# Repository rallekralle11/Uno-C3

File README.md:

Not intented as a wireless dev board but since it doesn't cost extra i added a crappy monopole antenna anyway. plenty of leftover space for it.

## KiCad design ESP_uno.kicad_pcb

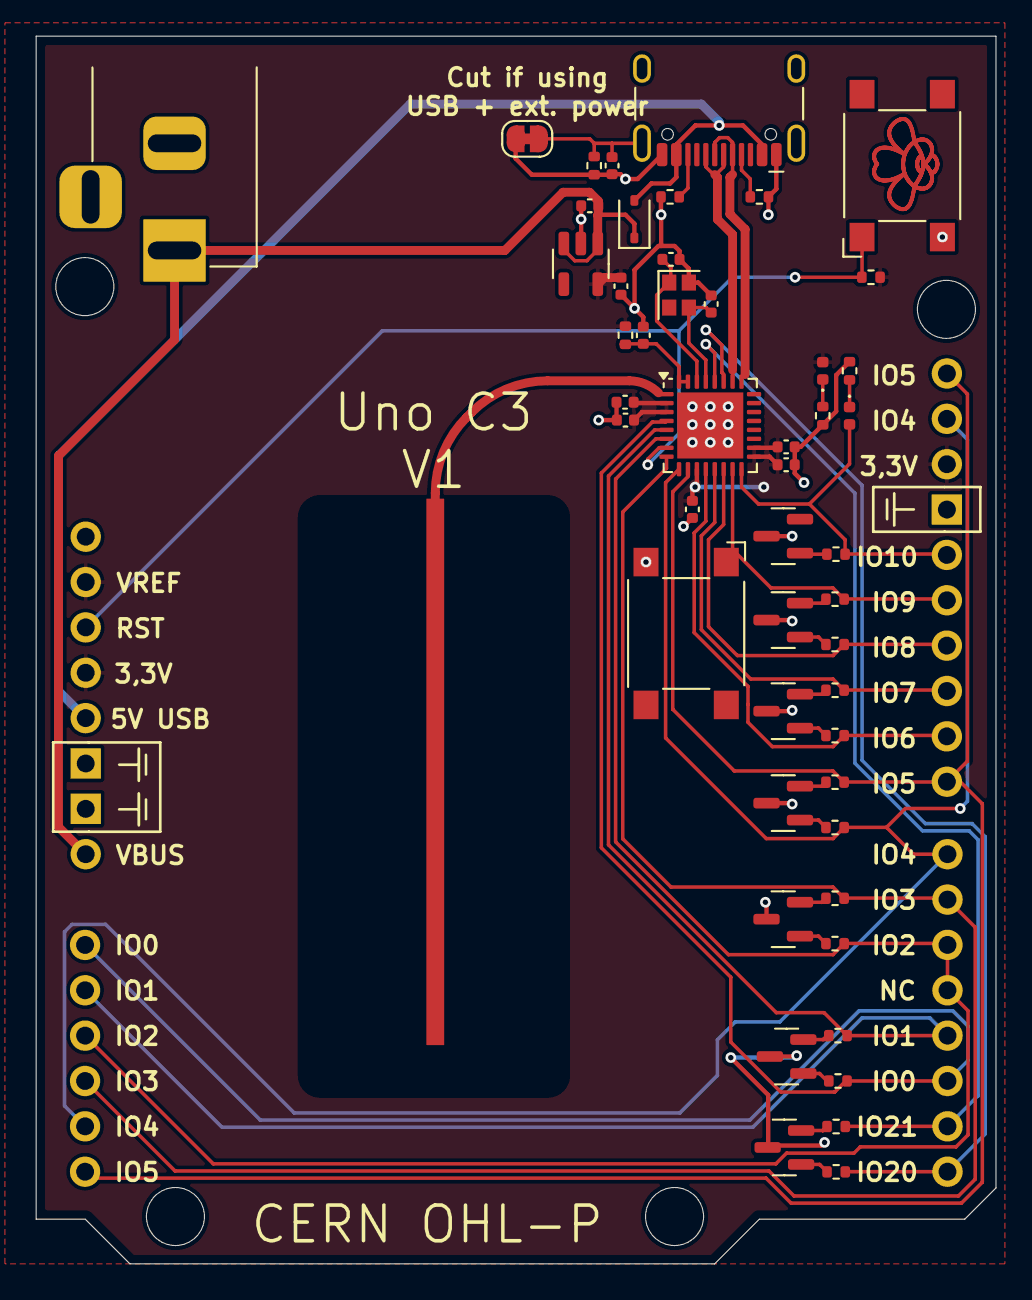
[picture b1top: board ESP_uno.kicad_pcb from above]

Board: 2 copper layers, 53.8 x 68.8 mm, 54 parts (0 on the bottom side), 42 nets.

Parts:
AE1: Antenna; TestPoint_Loop_D2.50mm_Drill1.0mm
C1, C2, C3, C4: TBD; C_0402_1005Metric
C5, C11: 100nF; C_0402_1005Metric
C6, C7, C8, C9, C10: C; C_0402_1005Metric
D1, D11: LED_Small; LED_0402_1005Metric
D2, D4, D5, D6, D7, D8, D9: D_Zener_Dual_CA; SOT-23
D3: D_Small; D_SOD-323
J1: USB_C_Receptacle_USB2.0_14P; USB_C_Receptacle_HCTL_HC-TYPE-C-16P-01A
J2: Barrel; BarrelJack_Horizontal
J3, J6: Conn_01x08; PinSocket_1x08_P2.54mm_Vertical
J4: Conn_01x10; PinSocket_1x10_P2.54mm_Vertical
J5: Conn_01x06; PinSocket_1x06_P2.54mm_Vertical
JP1: Jumper; SolderJumper-2_P1.3mm_Bridged_RoundedPad1.0x1.5mm
R1, R2, R3, R4, R5: 5,1k; R_0402_1005Metric
R6, R7, R8, R9, R10, R11, R12, R13, R14, R15, R17, R18, R19, R22, R23: 220; R_0402_1005Metric
SW1, SW2: SW_MEC_5G; SW_SPST_Omron_B3FS-100xP
U1: ESP32-C3; QFN-32-1EP_5x5mm_P0.5mm_EP3.7x3.7mm
U2: PAM2305AAB330; TSOT-23-5
Y1: 40MHz; Crystal_SMD_2016-4Pin_2.0x1.6mm

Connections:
+3.3V: C4.1, C6.1, C7.1, C8.1, C9.1, C10.1, D11.2 (A), J3.2, J3.4, J4.3, R4.2, R5.1, U1.2 (VDD3P3), U1.3 (VDD3P3), U1.11 (VDD3P3_RTC), U1.17 (VDD3P3_CPU), U1.18 (VDD_SPI), U2.5 (SW)
+5V: D3.2 (A), J1.A4 (VBUS), J1.A9 (VBUS), J1.B4 (VBUS), J1.B9 (VBUS), J3.5
D+: J1.A6 (D+), J1.B6 (D+), U1.26 (GPIO19)
D-: J1.A7 (D-), J1.B7 (D-), U1.25 (GPIO18)
GND: C1.2, C2.2, C3.2, C4.2, C5.2, C6.2, C7.2, C8.2, C9.2, C10.2, C11.2, D2.1 (A), D4.1 (A), D5.1 (A), D6.1 (A), D7.1 (A), D8.1 (A), D9.1 (A), J1.A1 (GND), J1.A12 (GND), J1.B1 (GND), J1.B12 (GND), J2.2, J3.6, J3.7, J4.4, JP1.2 (B), R1.2, R2.2, R3.1, R22.1, R23.1, SW1.2 (B), SW2.2 (B), U1.33 (GND), U2.2 (GND), Y1.2, Y1.4
IO0: J5.1, J6.6, R19.2, U1.4 (XTAL_32K_P)
IO1: J5.2, J6.5, R18.2, U1.5 (XTAL_32K_N)
IO2: J5.3, J6.3, J6.4, R9.2, U1.6 (GPIO2)
IO3: J5.4, J6.2, R8.2, U1.8 (GPIO3)
IO4: J4.2, J5.5, J6.1, R11.2, U1.9 (MTMS)
IO5: J4.1, J4.10, J5.6, R10.2, U1.10 (MTDI)
IO6: J4.9, R13.2, U1.12 (MTCK)
IO7: J4.8, R12.2, U1.13 (MTDO)
IO8: J4.7, R15.2, U1.14 (GPIO8)
IO9: J4.6, R14.2, SW1.1 (A), U1.15 (GPIO9)
IO10: D1.2 (A), J4.5, R17.2, U1.16 (GPIO10)
IO20: J6.8, R6.2, U1.27 (U0RXD)
IO21: J6.7, R7.2, U1.28 (U0TXD)
unnamed: AE1.1 (A), U1.1 (LNA_IN)
unnamed: C11.1, R5.2, U1.31 (VDDA), U1.32 (VDDA)
unnamed: D1.1 (K), R23.2
unnamed: D2.2 (K), R7.1
unnamed: D2.3 (K), R6.1
unnamed: D4.2 (K), R8.1
unnamed: D4.3 (K), R9.1
unnamed: D5.2 (K), R10.1
unnamed: D5.3 (K), R11.1
unnamed: D6.2 (K), R12.1
unnamed: D6.3 (K), R13.1
unnamed: D7.2 (K), R14.1
unnamed: D7.3 (K), R15.1
unnamed: D8.3 (K), R17.1
unnamed: D9.2 (K), R18.1
unnamed: D9.3 (K), R19.1
unnamed: D11.1 (K), R22.2
unnamed: J1.A5 (CC1), R1.1
unnamed: J1.B5 (CC2), R2.1
unnamed: C5.1, J1.S1 (SHIELD), JP1.1 (A), R3.2
unnamed: C2.1, U1.29 (XTAL_N), Y1.3
unnamed: C1.1, U1.30 (XTAL_P), Y1.1
RST: J3.3, R4.1, SW2.1 (A), U1.7 (CHIP_EN)
VBUS: C3.1, D3.1 (K), J2.1, J3.8, U2.1 (Vin), U2.3 (EN)

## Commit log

2024-09-09 init
2024-09-09 pictures
2024-09-09 better picture
2024-09-09 values

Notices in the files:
ESP_uno.kicad_pcb:
CERN OHL-P
